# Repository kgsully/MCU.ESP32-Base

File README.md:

# ESP32 Base Design
 ESP32 WROOM Based Base Design

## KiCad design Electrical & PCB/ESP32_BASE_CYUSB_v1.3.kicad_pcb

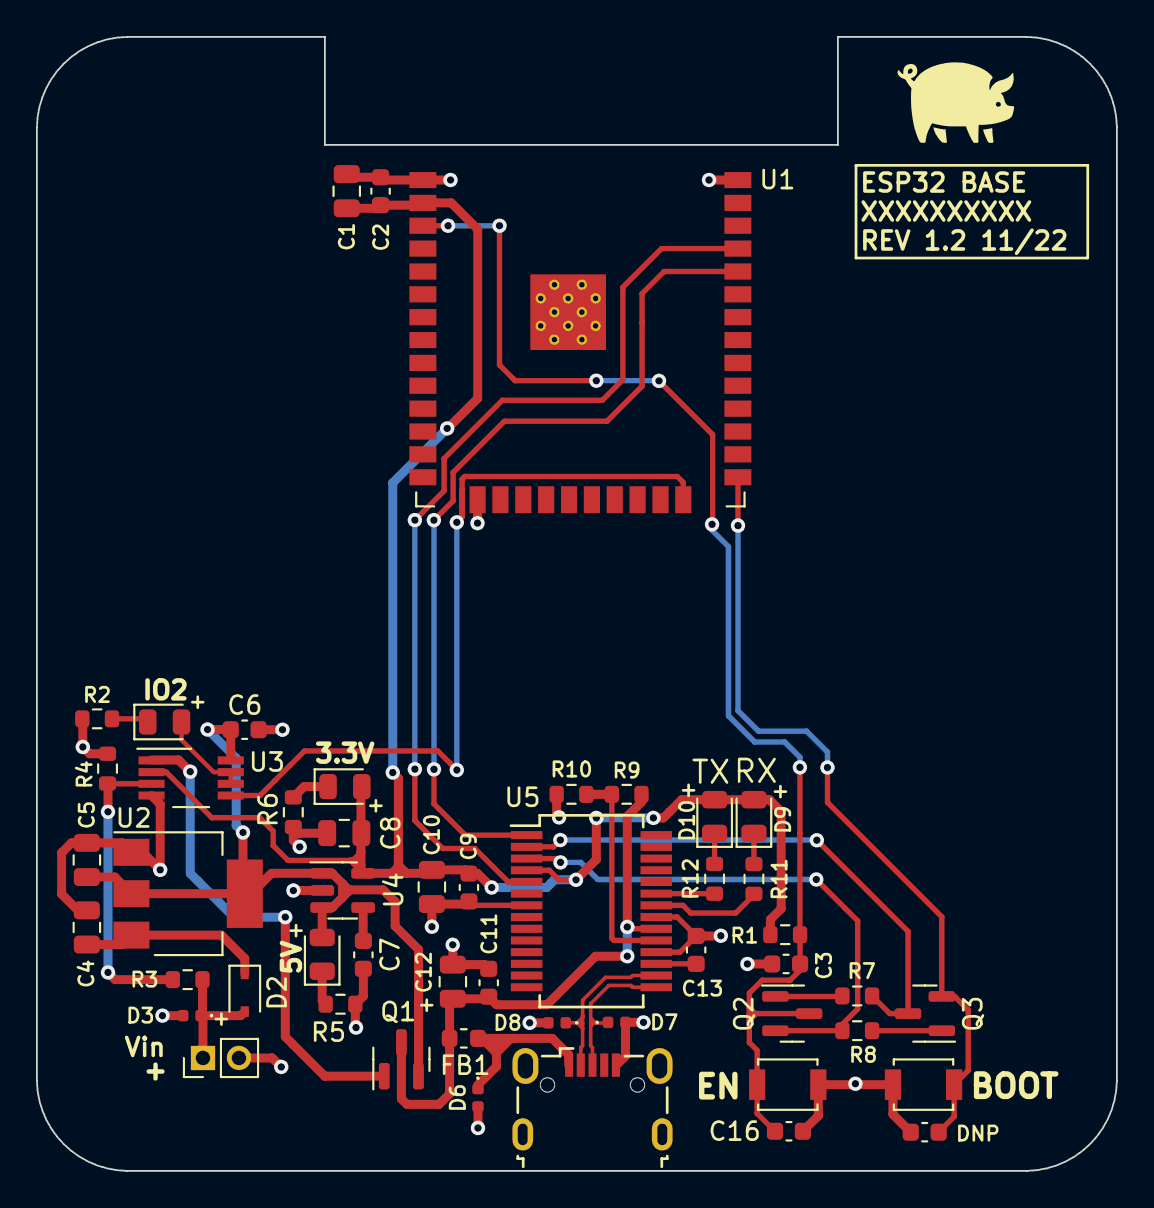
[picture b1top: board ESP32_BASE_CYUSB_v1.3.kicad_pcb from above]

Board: 2 copper layers, 60.0 x 63.0 mm, 54 parts (0 on the bottom side), 31 nets.

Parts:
C1: 22u; C_0805_2012Metric
C2, C3, C9, C11, C16: 0.1u; C_0603_1608Metric
C4: 1u; C_0805_2012Metric
C5: 4u7; C_0805_2012Metric
C6: 100n; C_0603_1608Metric
C7: 10n; C_0603_1608Metric
C8: 2.2u; C_0805_2012Metric
C10, C12: 4.7u; C_0805_2012Metric
C13: 1u; C_0603_1608Metric
C14: 0u; C_0603_1608Metric
D1: BLU; LED_0805_2012Metric
D2: BAT760-7; D_SOD-323
D3, D6, D7, D8: 5VWM; D_0402_1005Metric
D4: RED; LED_0805_2012Metric
D5, D9, D10: GRN; LED_0805_2012Metric
FB1: 40-100R; L_0603_1608Metric
H1, H2, H3, H4: MountingHole; MountingHole_3.2mm_M3
J2: Conn_01x02_Male; PinHeader_1x02_P2.00mm_Vertical
J3: USB_B_Micro; USB_Micro-B_Wuerth_629105150521
Q1: DMP2110U-7; SOT-23
Q2, Q3: SS8050-G; SOT-23
R1, R3, R4, R7, R8, R10: 10k; R_0603_1608Metric
R2: 470R; R_0603_1608Metric
R5, R6, R11, R12: 1k; R_0603_1608Metric
R9: 4k7; R_0603_1608Metric
SW1, SW2: SW_Push; SW_SPST_B3U-1000P
U1: ESP32-WROOM-32D; ESP32-WROOM-32
U2: LDL1117S50R; SOT-223-3_TabPin2
U3: LMV358IDGKR; VSSOP-8_3.0x3.0mm_P0.65mm
U4: SPX3819M5-L-3-3; SOT-23-5
U5: CY7C65213-28PVXI; SSOP-28_5.3x10.2mm_P0.65mm

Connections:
+3.3V: C1.1, C2.1, C8.1, C9.2, C10.1, D5.2 (A), D9.2 (A), D10.2 (A), R1.1, U1.2 (VDD), U3.2 (-), U4.5 (OUT), U5.4 (VCCIO)
+5V: C5.1, C6.1, D4.2 (A), Q1.2 (S), U2.2 (VO), U3.8 (V+), U4.1 (IN), U4.3 (EN)
/ESP32 MCU/DTR: Q3.3 (C), R7.1, U5.2 (DTR)
/ESP32 MCU/EN: C3.1, C16.2, Q2.3 (C), R1.2, SW2.2, U1.3 (EN)
/ESP32 MCU/IO0: C14.2, Q3.2 (E), SW1.2, U1.25 (IO0)
/ESP32 MCU/IO2: U1.24 (IO2), U3.5 (+)
/ESP32 MCU/RTS: Q2.2 (E), R8.2, U5.3 (RTS)
/ESP32 MCU/RXD: U1.35 (TXD0/IO1), U5.5 (RXD)
/ESP32 MCU/TXD: U1.34 (RXD0/IO3), U5.1 (TXD)
/Power Supply/VBUS: C11.2, C12.1, FB1.2, Q1.3 (D), R9.2, U5.20 (VCC)
/Power Supply/VIN: D2.2 (A), D3.1 (A1), J2.1, R3.1
/USB-UART Interface/USB_D+: D7.1 (A1), J3.3 (D+), U5.15 (USBDP)
/USB-UART Interface/USB_D-: D8.1 (A1), J3.2 (D-), U5.16 (USBDM)
GND: C1.2, C2.2, C3.2, C4.2, C5.2, C6.2, C7.2, C8.2, C9.1, C10.2, C11.1, C12.2, C13.2, C14.1, C16.1, D3.2 (A2), D6.2 (A2), D7.2 (A2), D8.2 (A2), J2.2, J3.5 (GND), R2.2, R4.2, R5.2, R6.2, R10.1, SW1.1, SW2.1, U1.1 (GND), U1.15 (GND), U1.38 (GND), U1.39 (GND), U2.1 (GND), U3.4 (V-), U4.2 (GND), U5.7 (GND), U5.18 (GND), U5.21 (GND)
unnamed: C4.1, D2.1 (K), U2.3 (VI)
unnamed: C7.1, U4.4 (BP)
unnamed: C13.1, U5.17 (VCCD)
unnamed: D1.1 (K), R2.1
unnamed: D1.2 (A), U3.6 (-), U3.7
unnamed: D4.1 (K), R5.1
unnamed: D5.1 (K), R6.1
unnamed: D6.1 (A1), FB1.1, J3.1 (VBUS)
unnamed: D9.1 (K), R11.2
unnamed: D10.1 (K), R12.2
unnamed: Q1.1 (G), U3.1
unnamed: Q2.1 (B), R7.2
unnamed: Q3.1 (B), R8.1
unnamed: R3.2, R4.1, U3.3 (+)
unnamed: R11.1, U5.22 (GPIO1)
unnamed: R12.1, U5.23 (GPIO0)
unnamed: R9.1, R10.2, U5.19 (~RESET)
